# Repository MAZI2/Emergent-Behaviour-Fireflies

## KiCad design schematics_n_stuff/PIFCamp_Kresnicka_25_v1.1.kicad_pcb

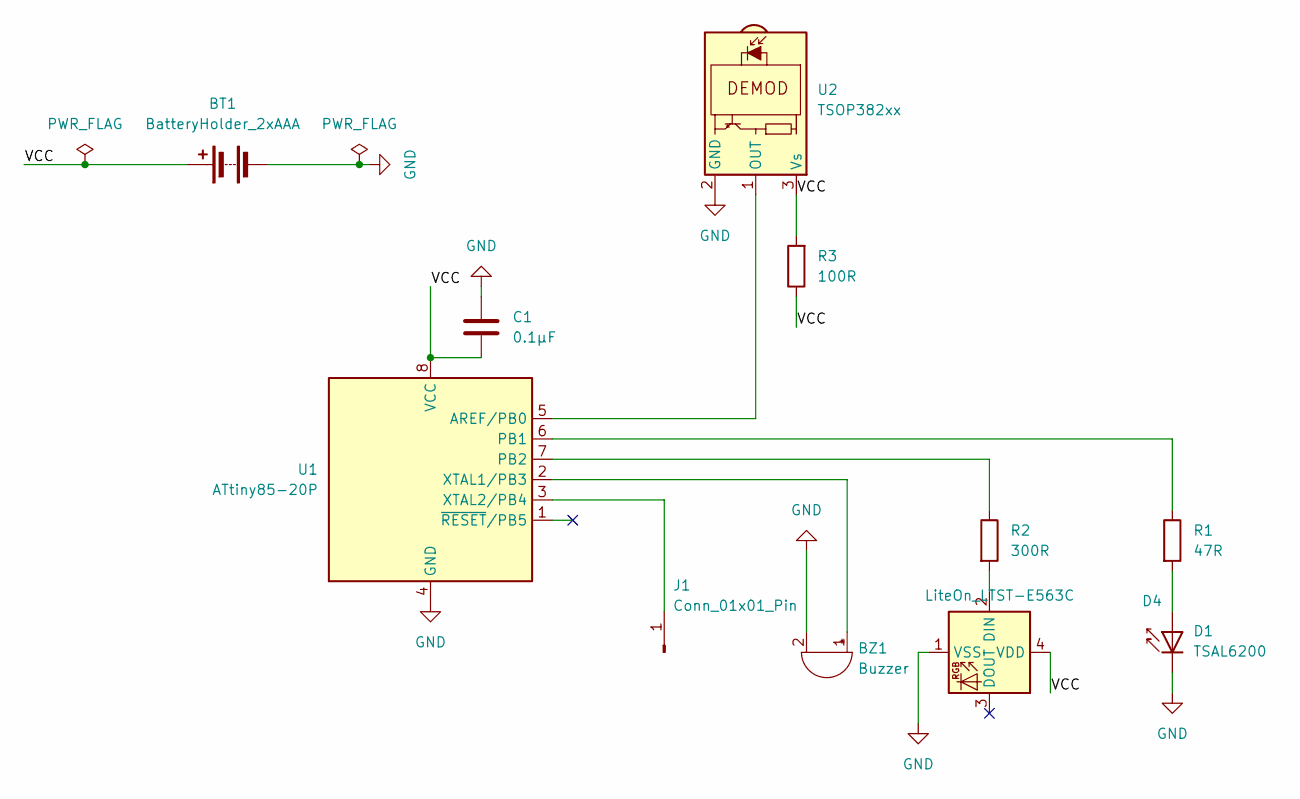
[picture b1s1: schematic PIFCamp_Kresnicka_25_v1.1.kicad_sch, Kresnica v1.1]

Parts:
BT1: BatteryHolder_2xAAA; TestPoint_2Pads_Pitch5.08mm_Drill1.3mm
BZ1: Buzzer; Buzzer_TDK_PS1240P02BT_D12.2mm_H6.5mm
C1: 0.1µF; C_1206_3216Metric_Pad1.33x1.80mm_HandSolder
D1: TSAL6200; LED_D3.0mm
D4: LiteOn_LTST-E563C; LED_D5.0mm-4_RGB_Wide_Pins
J1: Conn_01x01_Pin; TestPoint_Pad_1.0x1.0mm
R1: 47R; R_1206_3216Metric_Pad1.30x1.75mm_HandSolder
R2: 300R; R_1206_3216Metric_Pad1.30x1.75mm_HandSolder
R3: 100R; R_1206_3216Metric_Pad1.30x1.75mm_HandSolder
U1: ATtiny85-20P; DIP-8_W7.62mm_LongPads
U2: TSOP382xx; Vishay_MINICAST-3Pin

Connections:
/VCC: BT1.1 (+), C1.1, D4.4 (VDD), R3.1, R3.2, U1.8 (VCC), U2.3 (Vs)
GND: BT1.2 (-), BZ1.2 (-), C1.2, D1.1 (K), D4.1 (VSS), U1.4 (GND), U2.2 (GND)
unnamed: BZ1.1 (+), U1.2 (XTAL1/PB3)
unnamed: D1.2 (A), R1.2
unnamed: D4.2 (DIN), R2.2
unnamed: J1.1, U1.3 (XTAL2/PB4)
unnamed: U1.5 (AREF/PB0), U2.1 (OUT)
unnamed: R1.1, U1.6 (PB1)
unnamed: R2.1, U1.7 (PB2)

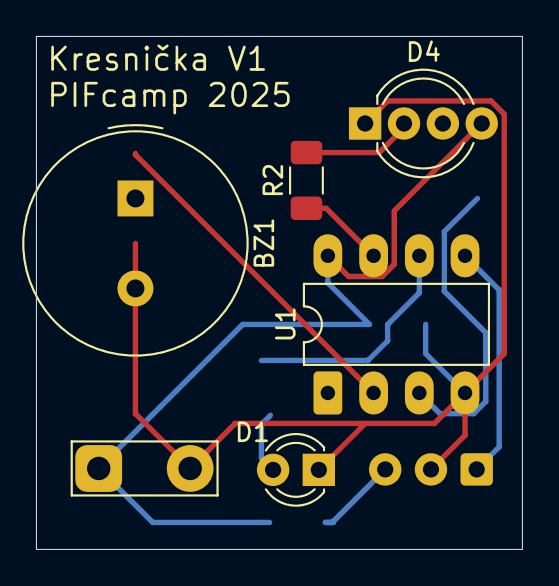
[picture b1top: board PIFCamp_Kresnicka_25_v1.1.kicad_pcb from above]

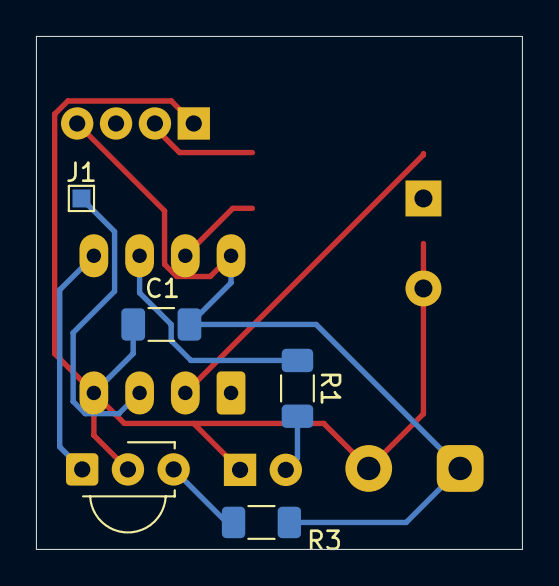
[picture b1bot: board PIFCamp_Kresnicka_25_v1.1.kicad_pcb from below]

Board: 2 copper layers, 27.0 x 28.5 mm, 11 parts (5 on the bottom side), 9 nets.

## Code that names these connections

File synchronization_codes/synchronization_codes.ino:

#include <Arduino.h>
#include <avr/io.h>
#include <stdint.h>
#include <Adafruit_NeoPixel.h>

#define NEOPIXEL_PIN  PB2
#define NUM_PIXELS    1
Adafruit_NeoPixel strip(NUM_PIXELS, NEOPIXEL_PIN, NEO_GRB + NEO_KHZ800);

// Behavior tuning
// #define PHASE_MAX 255
uint8_t PHASE_MAX = 255;
#define EPSILON 64
#define PHASE_STEP 1
#define TICK_DELAY_MS 2
#define JUMP_TO_FLASH_MARGIN 16
#define JITTER_INTERVAL 8

// Pins
#define IR_TX PB1
#define IR_RX PB0
#define LED   PB2
#define BUZZER PB3
// PB4

// Sanguine gradient
#define SANGUINE_START_R 255   // stronger red start
#define SANGUINE_START_G 0    // add some green for orange warmth
#define SANGUINE_START_B 0    // low blue

#define SANGUINE_END_R 255     // max red at end
#define SANGUINE_END_G 183     // more green for bright orange
#define SANGUINE_END_B 0

bool code_received = false;
uint32_t timer = 0;
uint32_t red_timer = 0;
bool red = false;

uint8_t state = 0;

uint32_t start_time;
uint32_t duration;
uint32_t decoding_start_time;
uint8_t code[8];
uint8_t code_num;


void setup() {
  // IR pins
  DDRB |= (1 << IR_TX);      // IR emitter as output
  DDRB &= ~(1 << IR_RX);     // IR receiver as input
  PORTB |= (1 << IR_RX);     // Enable pull-up on receiver
  
  // Configure LED and buzzer
  DDRB |= (1 << LED);        // LED as output
  DDRB |= (1 << BUZZER);     // Buzzer as output
  PORTB &= ~(1 << LED);      // LED off initially
  PORTB &= ~(1 << BUZZER);   // Buzzer off initially
  
  // Initialize NeoPixel
  strip.begin();
  strip.clear();
  strip.show();
}

void emit_pulse(uint16_t cycles) {
  for (uint16_t i = 0; i < cycles; i++) {
    PORTB |= (1 << IR_TX);
    delayMicroseconds(15);
    PORTB &= ~(1 << IR_TX);
    delayMicroseconds(15);
  }
}

static inline void mark_us(uint16_t us) {
  // carrier ON for us microseconds
  // reuse your emit_pulse: 1 cycle = 30us (15+15)
  uint16_t cycles = us / 30;
  if (cycles < 1) cycles = 1;
  emit_pulse(cycles);
}

static inline void space_us(uint16_t us) {
  // carrier OFF for us microseconds
  PORTB &= ~(1 << IR_TX);
  delayMicroseconds(us);
}

void send_code(uint8_t v) {
  // Start
  mark_us(6000);
  space_us(3000);

  // 8 bits MSB first
  for (int8_t i = 7; i >= 0; i--) {
    if (v & (1 << i)) {
      mark_us(2000);  // '1'
      space_us(2000);
    } else {
      mark_us(1000);  // '0'
      space_us(3000);
    }
  }

  // End gap (helps receiver reset between packets)
  space_us(6000);
}

void print_code() {
  for (int8_t i = 7; i >= 0; i--) {
    if (code_num & (1 << i)) {
      // Send '1' bit: pulse for 15us ON, 15us OFF
      // emit_pulse(60); // 1 cycle = 30us total (15us on + 15us off)
      PORTB |= (1 << PB4);
      delayMicroseconds(300);
    } else {
      // Send '0' bit: no pulse, just delay 30us (one cycle length)
      PORTB &= ~(1 << PB4);
      delayMicroseconds(300);
    }
  }
} 

void construct_code() {
  code_num = 0;
  for (uint8_t i = 4; i < 7; i++) {
    code_num = (code_num << 1) | code[i];
  }
  print_code();
}



void read_code() {
  bool is_high = false;

  if ((PINB & (1 << IR_RX)) == 0) {
    is_high = true;
  } else {
    is_high = false;
  }

  if (state == 0) {
    if (is_high) {
      start_time = micros();
      
      state = 1;
      code_received = false;
    }

  } else if (state == 1) {
    if (is_high) {
      duration = micros();
      if (duration - start_time > 2750) {
        decoding_start_time = micros() + 1600;
        state = 2;
      }
    } else {
      state = 0;
    }

  } else if (state == 2) {
    int32_t delta = micros() - decoding_start_time; // ensure 32-bit
    int8_t slot = (delta * 8) / 14500; // maps [0,2249] -> [0,7]
    
    if (slot > 7) slot = 7;

    if (slot > 0) code[slot] = is_high;

    if (slot >= 7) {
      construct_code();
      code_received = true;
      state = 0;
    }
  }
}

void phase_rgb_sanguine(uint8_t phase) {
  uint8_t r = SANGUINE_START_R + ((uint16_t)(SANGUINE_END_R - SANGUINE_START_R) * phase) / PHASE_MAX;
  uint8_t g = SANGUINE_START_G + ((uint16_t)(SANGUINE_END_G - SANGUINE_START_G) * phase) / PHASE_MAX;
  uint8_t b = SANGUINE_START_B + ((uint16_t)(SANGUINE_END_B - SANGUINE_START_B) * phase) / PHASE_MAX;

  if (red) {
    r = 255;
    g = 0;
    b = 0;
  }

  strip.setPixelColor(0, strip.Color(g, r, b));
  strip.show();
}

void beep(uint8_t tone) {
  uint8_t i;
  // Buzzer tone generation for ~100ms
  for (i = 0; i < 100; i++) {
    PORTB |= (1 << BUZZER);
    delayMicroseconds(tone);
    PORTB &= ~(1 << BUZZER);
    delayMicroseconds(tone);
  }
}

void flash_led_rgb() {
  uint8_t r = 255;//rand() % 256;
  uint8_t g = 100; //rand() % 256;
  uint8_t b = 0; //rand() % 256;

  strip.setPixelColor(0, strip.Color(g, r, b));
  strip.show();

  // delay(100);

  // strip.setPixelColor(0, strip.Color(0, 0, 0));
  // strip.show();
}



int main(void) {
  init();   // sets up Timer0 etc
  sei();    // enable interrupts
  // cli(); 
  setup();
  // sei();

  uint8_t phase = 0;
  uint8_t last_rx_state = (PINB & (1 << IR_RX));
  uint8_t refractory = 0;
  uint8_t jitter_tick = 0;

  while (1) {
    delay(TICK_DELAY_MS);
    // phase += PHASE_STEP;

    // uint32_t time = micros();

    // if (time - red_timer < 10000) {
    //   red = true;
    // } else {
    //   red = false;
    //   code_num = 0;
    // }

    // read_code();

    // if (code_num == 5) {
    //   red_timer = micros();
    //   phase += random(0, 255);
    // }

    // if (time - timer > 2000) {
    //   timer = time;

    phase += PHASE_STEP;
  
    if (phase > PHASE_MAX) phase = PHASE_MAX;

    if (phase >= PHASE_MAX) {
      // emit_pulse(200);
      send_code(170);
      flash_led_rgb();
      // beep(phase);

      phase = 0;
      refractory = 170;
    }
    
    phase_rgb_sanguine(phase);
    // flash_led_rgb();
    
    uint8_t current_rx = (PINB & (1 << IR_RX));
    // if (last_rx_state && !current_rx && refractory == 0) {
    //   if (phase > (PHASE_MAX / 4)) {
    //     uint8_t delta = ((uint16_t)EPSILON * (PHASE_MAX - phase)) / PHASE_MAX;
    //     phase += delta;
    //     if (phase > PHASE_MAX) phase = PHASE_MAX;

    //     // Check if close enough to flash immediately
    //     if (PHASE_MAX - phase < JUMP_TO_FLASH_MARGIN) {
    //       emit_pulse(200);
    //       flash_led_rgb();
    //       phase = 0;
    //       refractory = 20;
    //     } else {
    //       refractory = 10;
    //     }
    //   }
    // }

    if (refractory > 0) refractory--;
    last_rx_state = current_rx;
    // }
  }
}

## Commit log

2025-07-03 submitted code
2025-07-04 syncro
2025-07-06 --RGB--
2025-07-07 pcb and schematics
2025-07-08 updated pcb
2025-07-08 wider tracks
2025-07-19 panelized
2025-07-24 simulation script
2025-07-29 finals
2025-07-30 Added random freq test
2025-07-30 chirping added
2025-07-31 codes
2025-08-01 Added various modes
2025-08-01 merged
2025-08-01 Prdulja disrupt
2025-08-01 disruptors
2025-08-01 4min
2025-08-01 Added color gradient cycling
2025-08-01 final
2026-02-02 reorder repo and make decoding more robust
2026-02-02 control beacon
2026-02-02 finished
2026-02-02 symmetric on/off and file rename
2026-02-02 colors for control beam debugging
2026-02-02 handheld control
2026-02-03 robustness update
2026-05-09 measurements and optimizations
2026-05-09 patch
2026-05-13 watchdog patch
2026-05-13 patches
2026-05-18 make beacons look liek fireflies
2026-05-18 fix control beacon
2026-05-18 settings
2026-05-28 Add fallback timer for sleep transition
2026-05-28 Extend TURN_ON propagation and sleep listen window
